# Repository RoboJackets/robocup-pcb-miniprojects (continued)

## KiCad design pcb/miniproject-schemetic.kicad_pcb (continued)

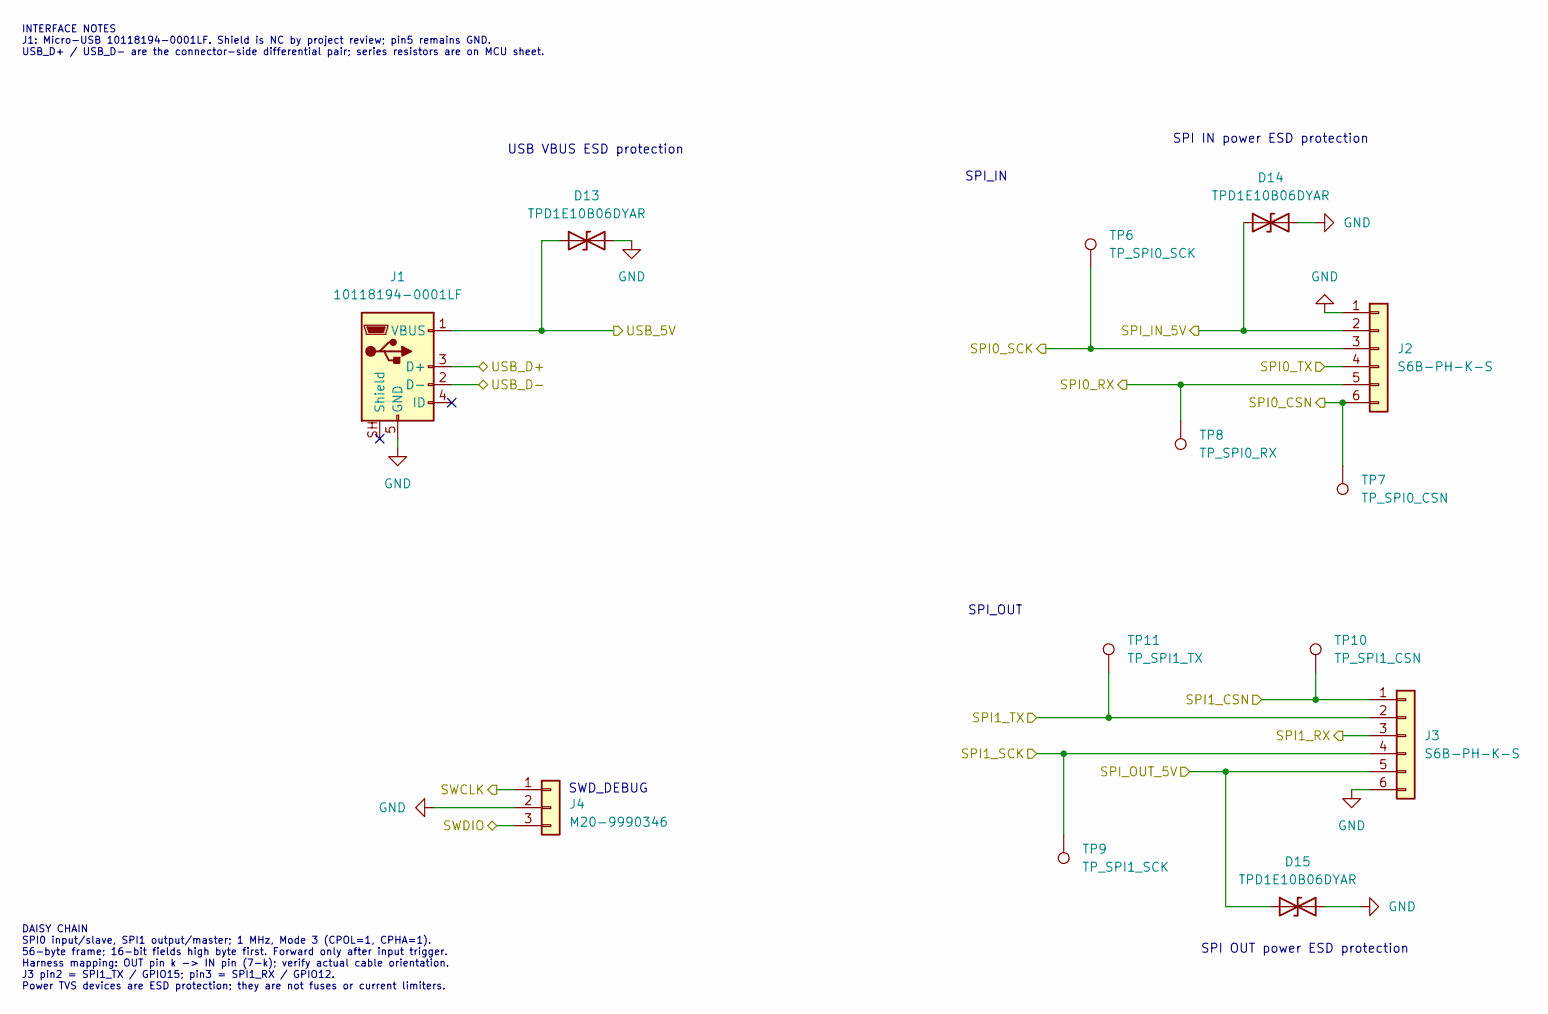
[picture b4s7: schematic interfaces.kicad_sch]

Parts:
D13, D14, D15: TPD1E10B06DYAR; D_SOD-523
J1: 10118194-0001LF; USB_Micro-B_Amphenol_10118194-0001LF_Horizontal
J2, J3: S6B-PH-K-S; JST_PH_S6B-PH-K_1x06_P2.00mm_Horizontal
J4: M20-9990346; PinHeader_1x03_P2.54mm_Vertical
TP6: TP_SPI0_SCK; TestPoint_Pad_D1.0mm
TP7: TP_SPI0_CSN; TestPoint_Pad_D1.0mm
TP8: TP_SPI0_RX; TestPoint_Pad_D1.0mm
TP9: TP_SPI1_SCK; TestPoint_Pad_D1.0mm
TP10: TP_SPI1_CSN; TestPoint_Pad_D1.0mm
TP11: TP_SPI1_TX; TestPoint_Pad_D1.0mm

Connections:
+5V: D15.1 (A1), J3.5; also elsewhere on the board
/Interfaces/USB_D+: J1.3 (D+); also elsewhere on the board
/Interfaces/USB_D-: J1.2 (D-); also elsewhere on the board
/SPI0_CSN: J2.6, TP7.1 (1_1); also elsewhere on the board
/SPI0_RX: J2.5, TP8.1 (1_1); also elsewhere on the board
/SPI0_SCK: J2.3, TP6.1 (1_1); also elsewhere on the board
/SPI0_TX: J2.4; also elsewhere on the board
/SPI1_CSN: J3.1, TP10.1 (1_1); also elsewhere on the board
/SPI1_RX: J3.3; also elsewhere on the board
/SPI1_SCK: J3.4, TP9.1 (1_1); also elsewhere on the board
/SPI1_TX: J3.2, TP11.1 (1_1); also elsewhere on the board
/SPI_IN_5V: D14.1 (A1), J2.2; also elsewhere on the board
/SWCLK: J4.1; also elsewhere on the board
/SWDIO: J4.3; also elsewhere on the board
/USB_5V: D13.1 (A1), J1.1 (VBUS); also elsewhere on the board
GND: D13.2 (A2), D14.2 (A2), D15.2 (A2), J1.5 (GND), J2.1, J3.6, J4.2; also elsewhere on the board

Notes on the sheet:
USB VBUS ESD protection
SPI_IN
SPI OUT power ESD protection
SPI IN power ESD protection
SPI_OUT
SWD_DEBUG
INTERFACE NOTES J1: Micro-USB 10118194-0001LF. Shield is NC by project review; pin5 remains GND. USB_D+ / USB_D- are the connector-side differential pair; series resistors are on MCU sheet.
DAISY CHAIN SPI0 input/slave, SPI1 output/master; 1 MHz, Mode 3 (CPOL=1, CPHA=1). 56-byte frame; 16-bit fields high byte first. Forward only after input trigger. Harness mapping: OUT pin k -> IN pin (7-k); verify actual cable orientation. J3 pin2 = SPI1_TX / GPIO15; pin3 = SPI1_RX / GPIO12. Power T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

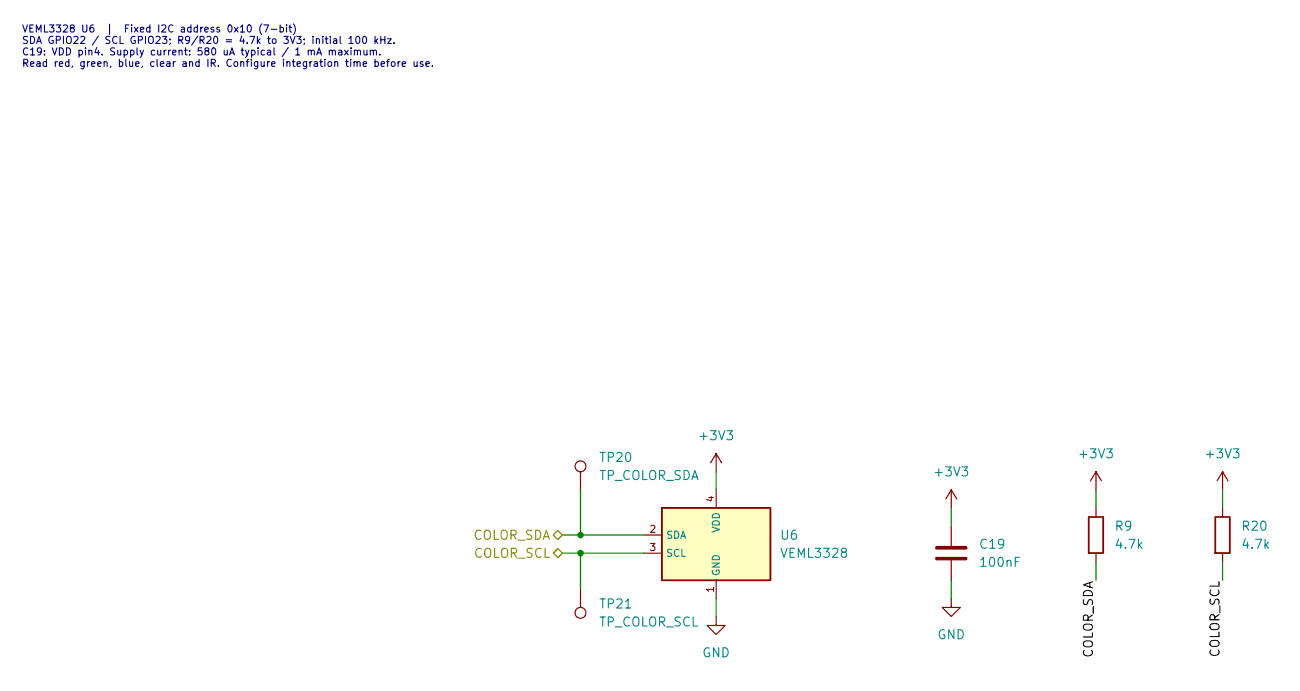
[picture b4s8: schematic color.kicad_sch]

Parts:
C19: 100nF; C_0603_1608Metric; Tolerance 10%; Voltage 6.3V minimum
R9, R20: 4.7k; R_0603_1608Metric; Tolerance 1%
TP20: TP_COLOR_SDA; TestPoint_Pad_D1.0mm
TP21: TP_COLOR_SCL; TestPoint_Pad_D1.0mm
U6: VEML3328; Vishay_VEML3328_2x1.25mm

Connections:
+3V3: C19.1, R9.1, R20.1, U6.4 (VDD); also elsewhere on the board
/COLOR_SCL: R20.2, TP21.1 (1_1), U6.3 (SCL); also elsewhere on the board
/COLOR_SDA: R9.2, TP20.1 (1_1), U6.2 (SDA); also elsewhere on the board
GND: C19.2, U6.1 (GND); also elsewhere on the board

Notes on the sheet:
VEML3328 U6 | Fixed I2C address 0x10 (7-bit) SDA GPIO22 / SCL GPIO23; R9/R20 = 4.7k to 3V3; initial 100 kHz. C19: VDD pin4. Supply current: 580 uA typical / 1 mA maximum. Read red, green, blue, clear and IR. Configure integration time before use.

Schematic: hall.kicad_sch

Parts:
C17: 100nF; C_0603_1608Metric; Tolerance 10%; Voltage 6.3V minimum
R15, R16, R17: 4.7k; R_0603_1608Metric; Tolerance 1%
TP18: TP_HALL_SCL; TestPoint_Pad_D1.0mm
TP19: TP_HALL_SDA; TestPoint_Pad_D1.0mm
U4: TMAG5273A2QDBVR; SOT-23-6

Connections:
+3V3: C17.1, R15.2, R16.1, R17.1, U4.4 (VCC); also elsewhere on the board
/HALL_SCL: R15.1, TP18.1 (1_1), U4.1 (SCL); also elsewhere on the board
/HALL_SDA: R16.2, TP19.1 (1_1), U4.6 (SDA); also elsewhere on the board
GND: C17.2, U4.2 (GND), U4.3 (TEST); also elsewhere on the board
unnamed: R17.2, U4.5 (~INT)

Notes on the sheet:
TMAG5273A2 U4 | Factory I2C address 0x35 (7-bit) SDA GPIO20 / SCL GPIO21; R15/R16 = 4.7k to 3V3; initial 100 kHz. A2 range option: +/-133 mT or +/-266 mT. Active current: 2.3 mA typical. C17: VCC pin4; TEST pin3 is GND. INT pin5 has R17 pullup only, no MCU IRQ. Firmware: INT_MODE = 0; use I2C trigg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

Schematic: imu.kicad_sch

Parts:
C20: 10nF; C_0603_1608Metric; Tolerance 10%; Voltage 6.3V minimum
C21: 100nF; C_0603_1608Metric; Tolerance 10%; Voltage 6.3V minimum
C22: 2.2µF; C_0603_1608Metric; Tolerance 10%; Voltage 6.3V minimum
R21, R22: 4.7k; R_0603_1608Metric; Tolerance 1%
TP14: TP_IMU_SDA; TestPoint_Pad_D1.0mm
TP15: TP_IMU_SCL; TestPoint_Pad_D1.0mm
U7: ICM-42605; LGA-14_3x2.5mm_P0.5mm_LayoutBorder3x4y

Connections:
+3V3: C20.1, C21.1, C22.1, R21.1, R22.1, U7.5 (VDDIO), U7.8 (VDD), U7.12 (~AP_CS); also elsewhere on the board
/IMU_SCL: R22.2, TP15.1 (1_1), U7.13 (AP_SCL); also elsewhere on the board
/IMU_SDA: R21.2, TP14.1 (1_1), U7.14 (AP_SDA); also elsewhere on the board
GND: C20.2, C21.2, C22.2, U7.1 (AP_AD0/SDO), U7.6 (GND), U7.7 (RESV), U7.9 (INT2/FSYNC); also elsewhere on the board

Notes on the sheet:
VDDIO, pin5
VDD, pin8
ICM-42605 U7 | I2C address 0x68 (7-bit), AP_AD0 pin1 = GND AP_CS pin12 = 3V3 for I2C. SDA GPIO16 / SCL GPIO17; R21/R22 = 4.7k. Initial bus speed 100 kHz. AP_AD0 is an input in this configuration. INT1 pin4 is NC. Pin9 is unused FSYNC: GND per TDK pin-function table. Firmware must keep pin9 as an in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

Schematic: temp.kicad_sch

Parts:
C18: 100nF; C_0603_1608Metric; Tolerance 10%; Voltage 6.3V minimum
R18, R19: 4.7k; R_0603_1608Metric; Tolerance 1%
TP16: TP_TEMP_SDA; TestPoint_Pad_D1.0mm
TP17: TP_TEMP_SCL; TestPoint_Pad_D1.0mm
U5: LM75ADP; TSSOP-8_3x3mm_P0.65mm

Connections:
+3V3: C18.1, R18.1, R19.1, U5.8 (VCC); also elsewhere on the board
/TEMP_SCL: R19.2, TP17.1 (1_1), U5.2 (SCL); also elsewhere on the board
/TEMP_SDA: R18.2, TP16.1 (1_1), U5.1 (SDA); also elsewhere on the board
GND: C18.2, U5.4 (GND), U5.5 (A2), U5.6 (A1), U5.7 (A0); also elsewhere on the board

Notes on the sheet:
LM75ADP U5 | I2C address 0x48 (7-bit), A2:A0 = 000 SDA GPIO18 / SCL GPIO19; R18/R19 = 4.7k to 3V3; initial 100 kHz. C18: VCC pin8. OS pin3 is NC; poll temperature over I2C. Supply current: 100 uA typical with inactive bus; 1 mA maximum with active bus. NXP LM75A register format: signed temperature;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

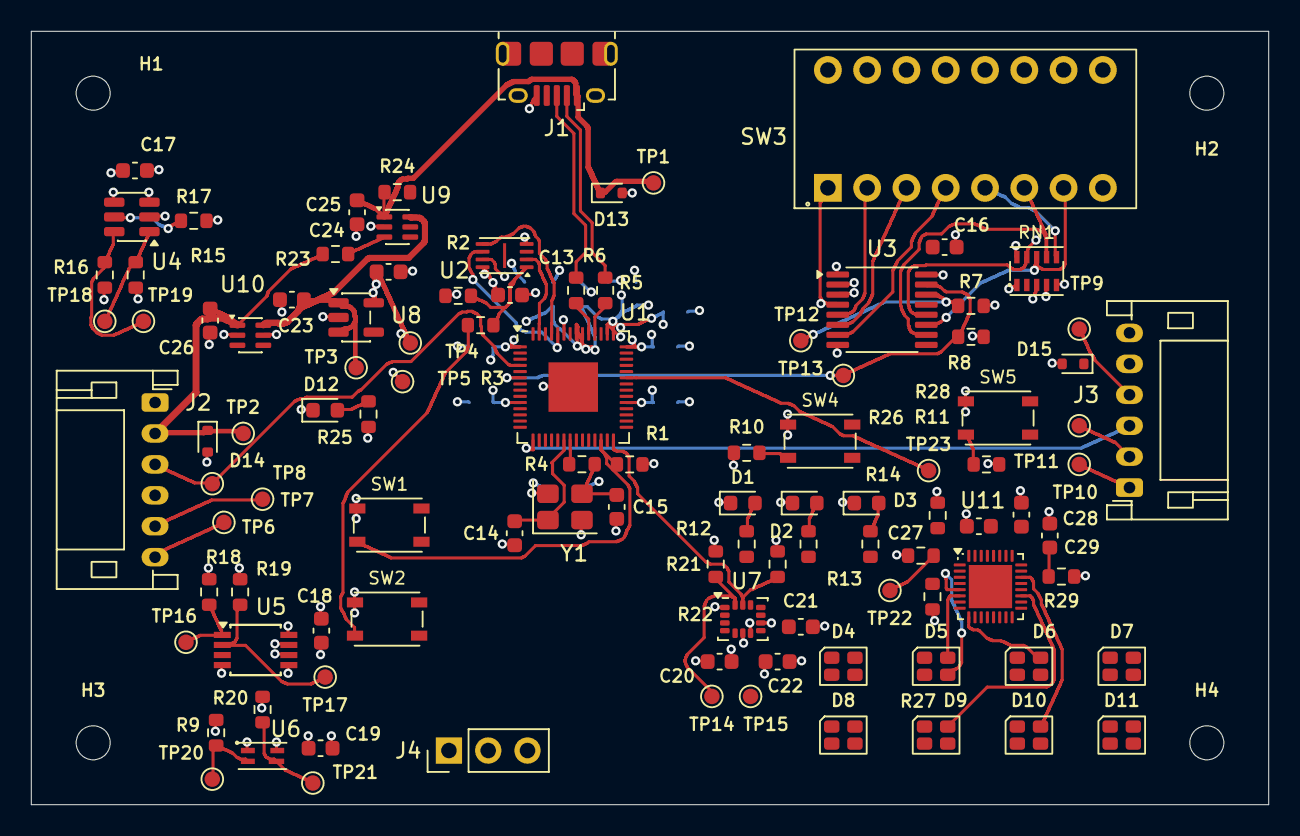
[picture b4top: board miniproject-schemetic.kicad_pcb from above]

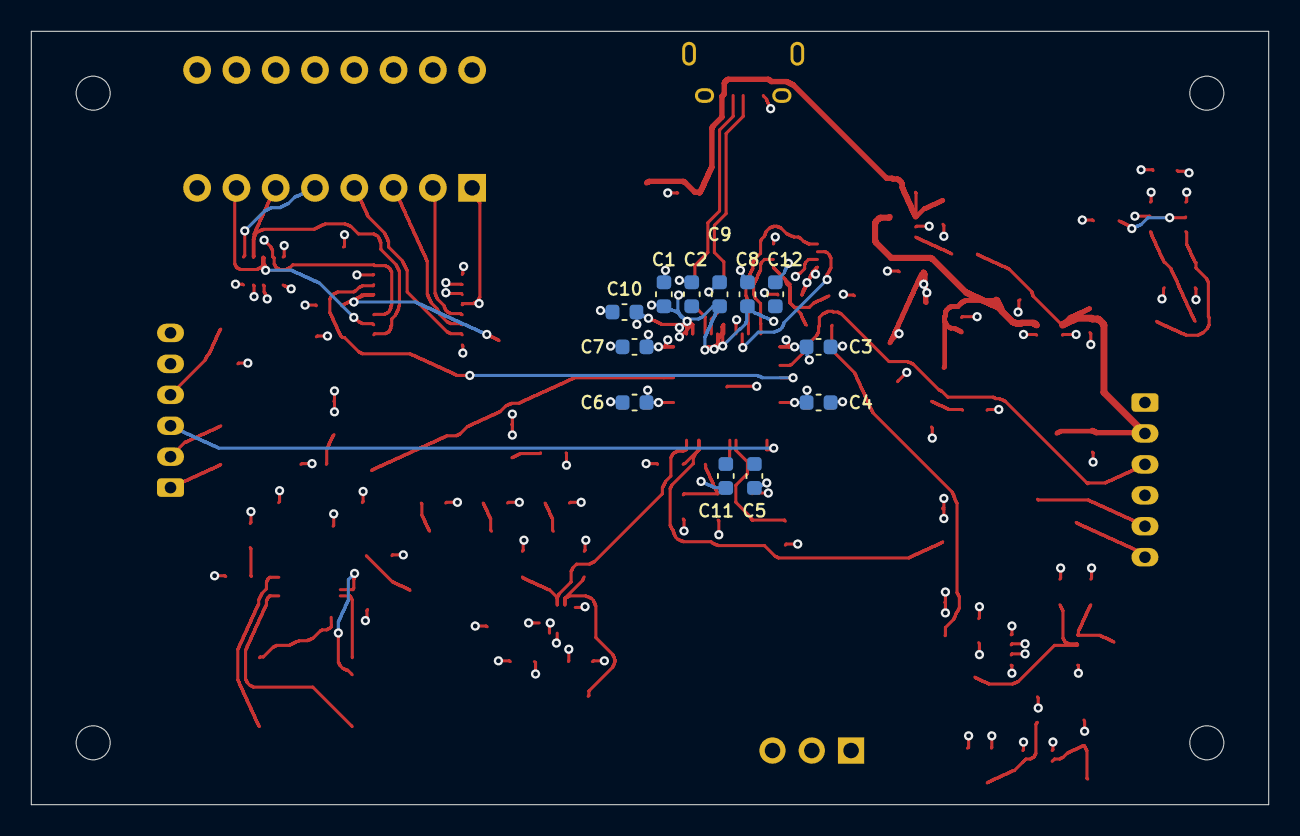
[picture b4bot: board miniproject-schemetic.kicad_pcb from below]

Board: 4 copper layers, 80.0 x 50.0 mm, 122 parts (12 on the bottom side), 89 nets.

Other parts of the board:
H1, H2, H3, H4: MountingHole_2.2mm_M2

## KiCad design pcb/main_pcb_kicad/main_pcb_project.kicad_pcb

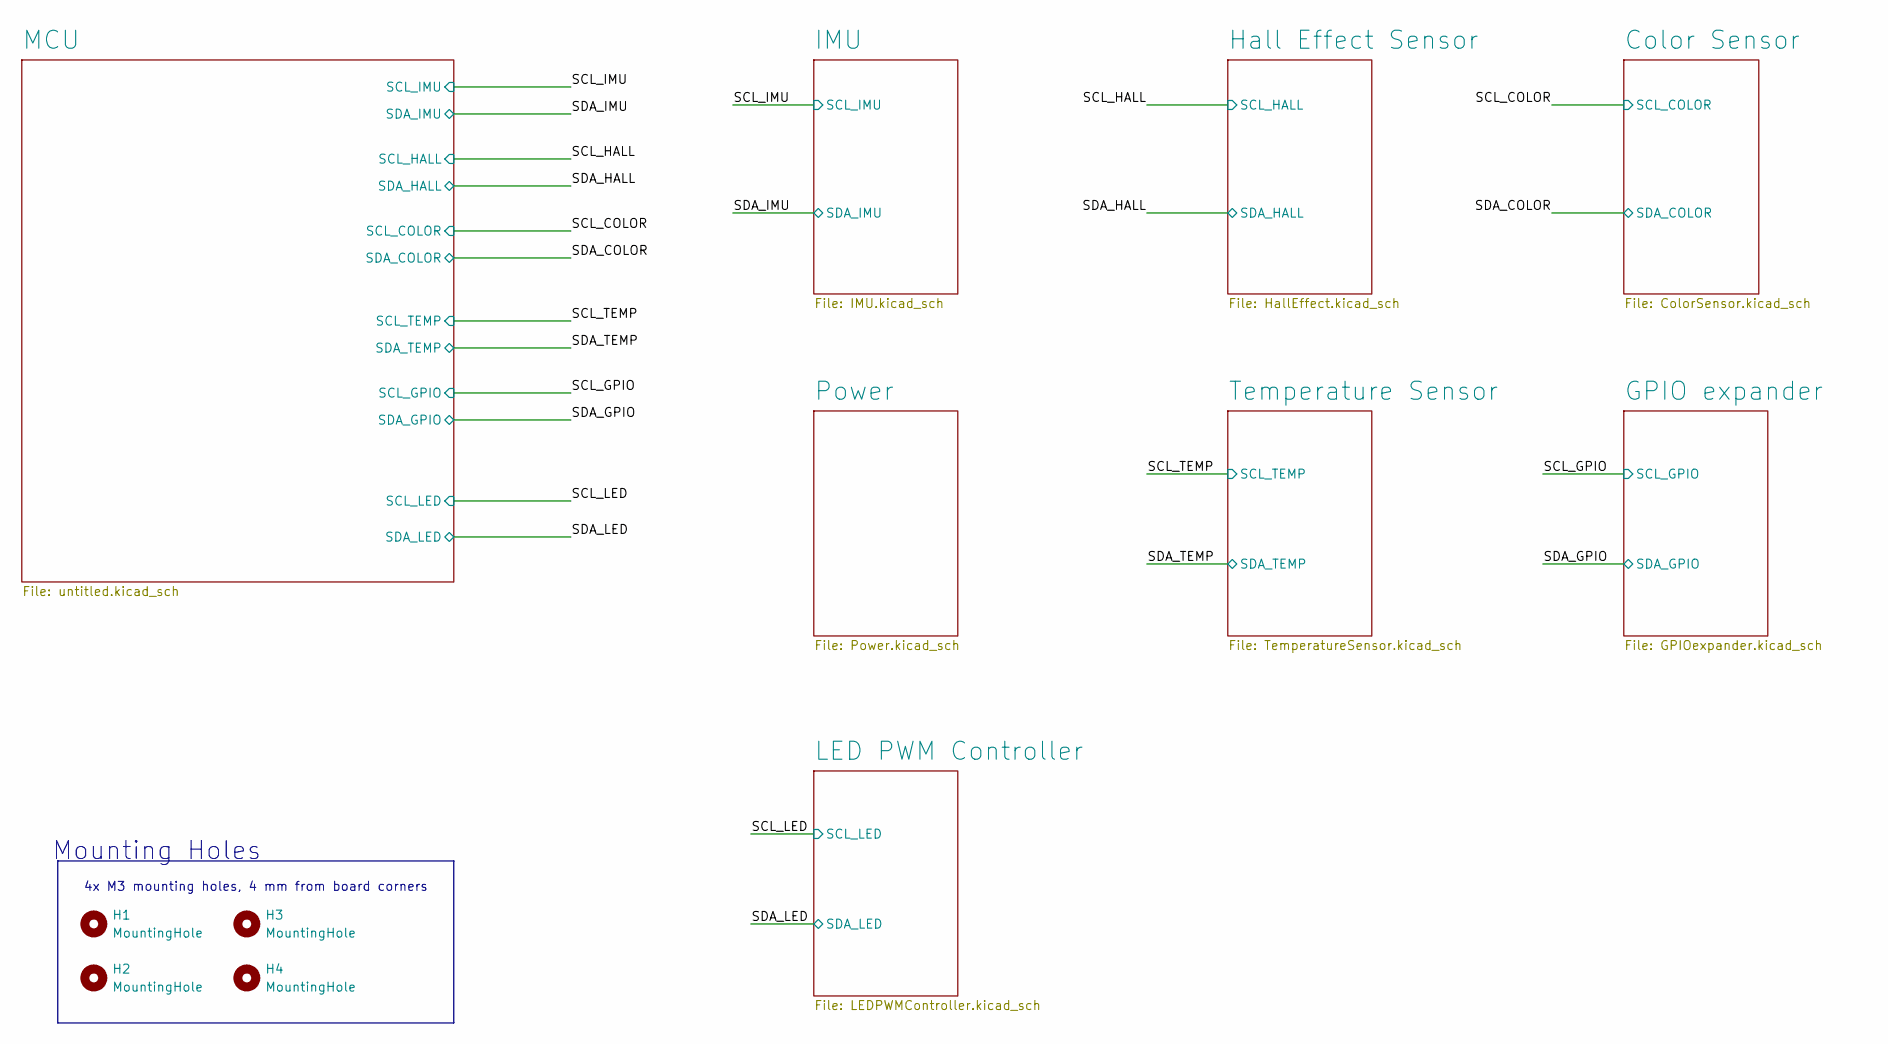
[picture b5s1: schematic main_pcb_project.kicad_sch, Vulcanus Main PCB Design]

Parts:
H1, H2, H3, H4: MountingHole; MountingHole_3.2mm_M3

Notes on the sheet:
Mounting Holes
4x M3 mounting holes, 4 mm from board corners

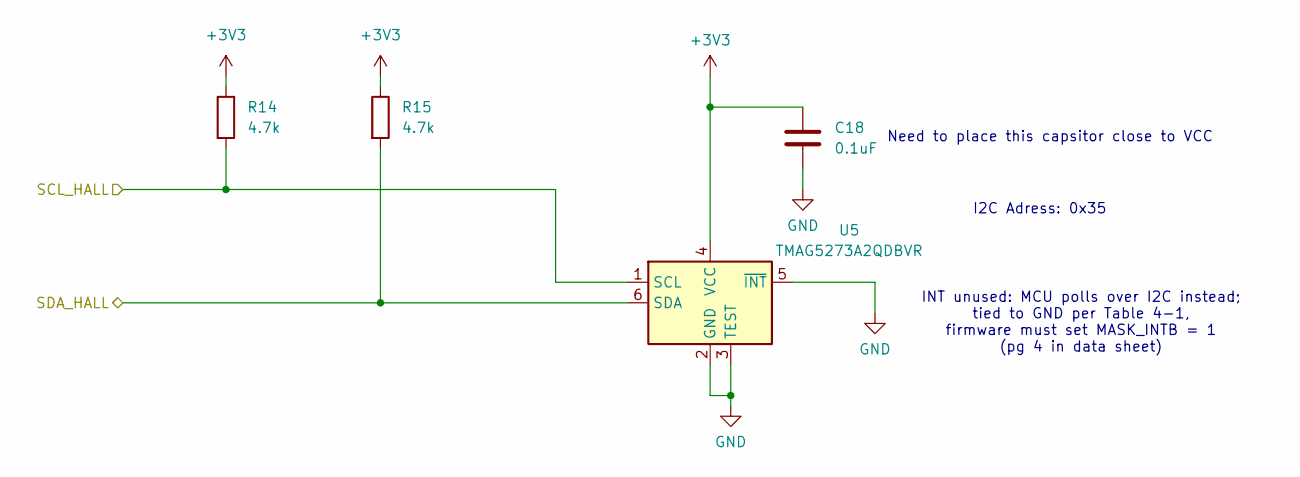
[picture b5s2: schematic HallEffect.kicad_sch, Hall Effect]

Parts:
C18: 0.1uF; C_0603_1608Metric; Manufacturer P/N CL10B104KB8NNNC
R14, R15: 4.7k; R_0402_1005Metric; Manufacturer P/N RC0402FR-074K7L
U5: TMAG5273A2QDBVR; SOT-23-6; Manufacturer P/N TMAG5273A2QDBVR

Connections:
+3V3: C18.1, R14.1, R15.1, U5.4 (VCC); also elsewhere on the board
/SCL_HALL: R14.2, U5.1 (SCL); also elsewhere on the board
/SDA_HALL: R15.2, U5.6 (SDA); also elsewhere on the board
GND: C18.2, U5.2 (GND), U5.3 (TEST), U5.5 (~INT); also elsewhere on the board

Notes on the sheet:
INT unused: MCU polls over I2C instead; tied to GND per Table 4-1, firmware must set MASK_INTB = 1 (pg 4 in data sheet)
Need to place this capsitor close to VCC
I2C Adress: 0x35

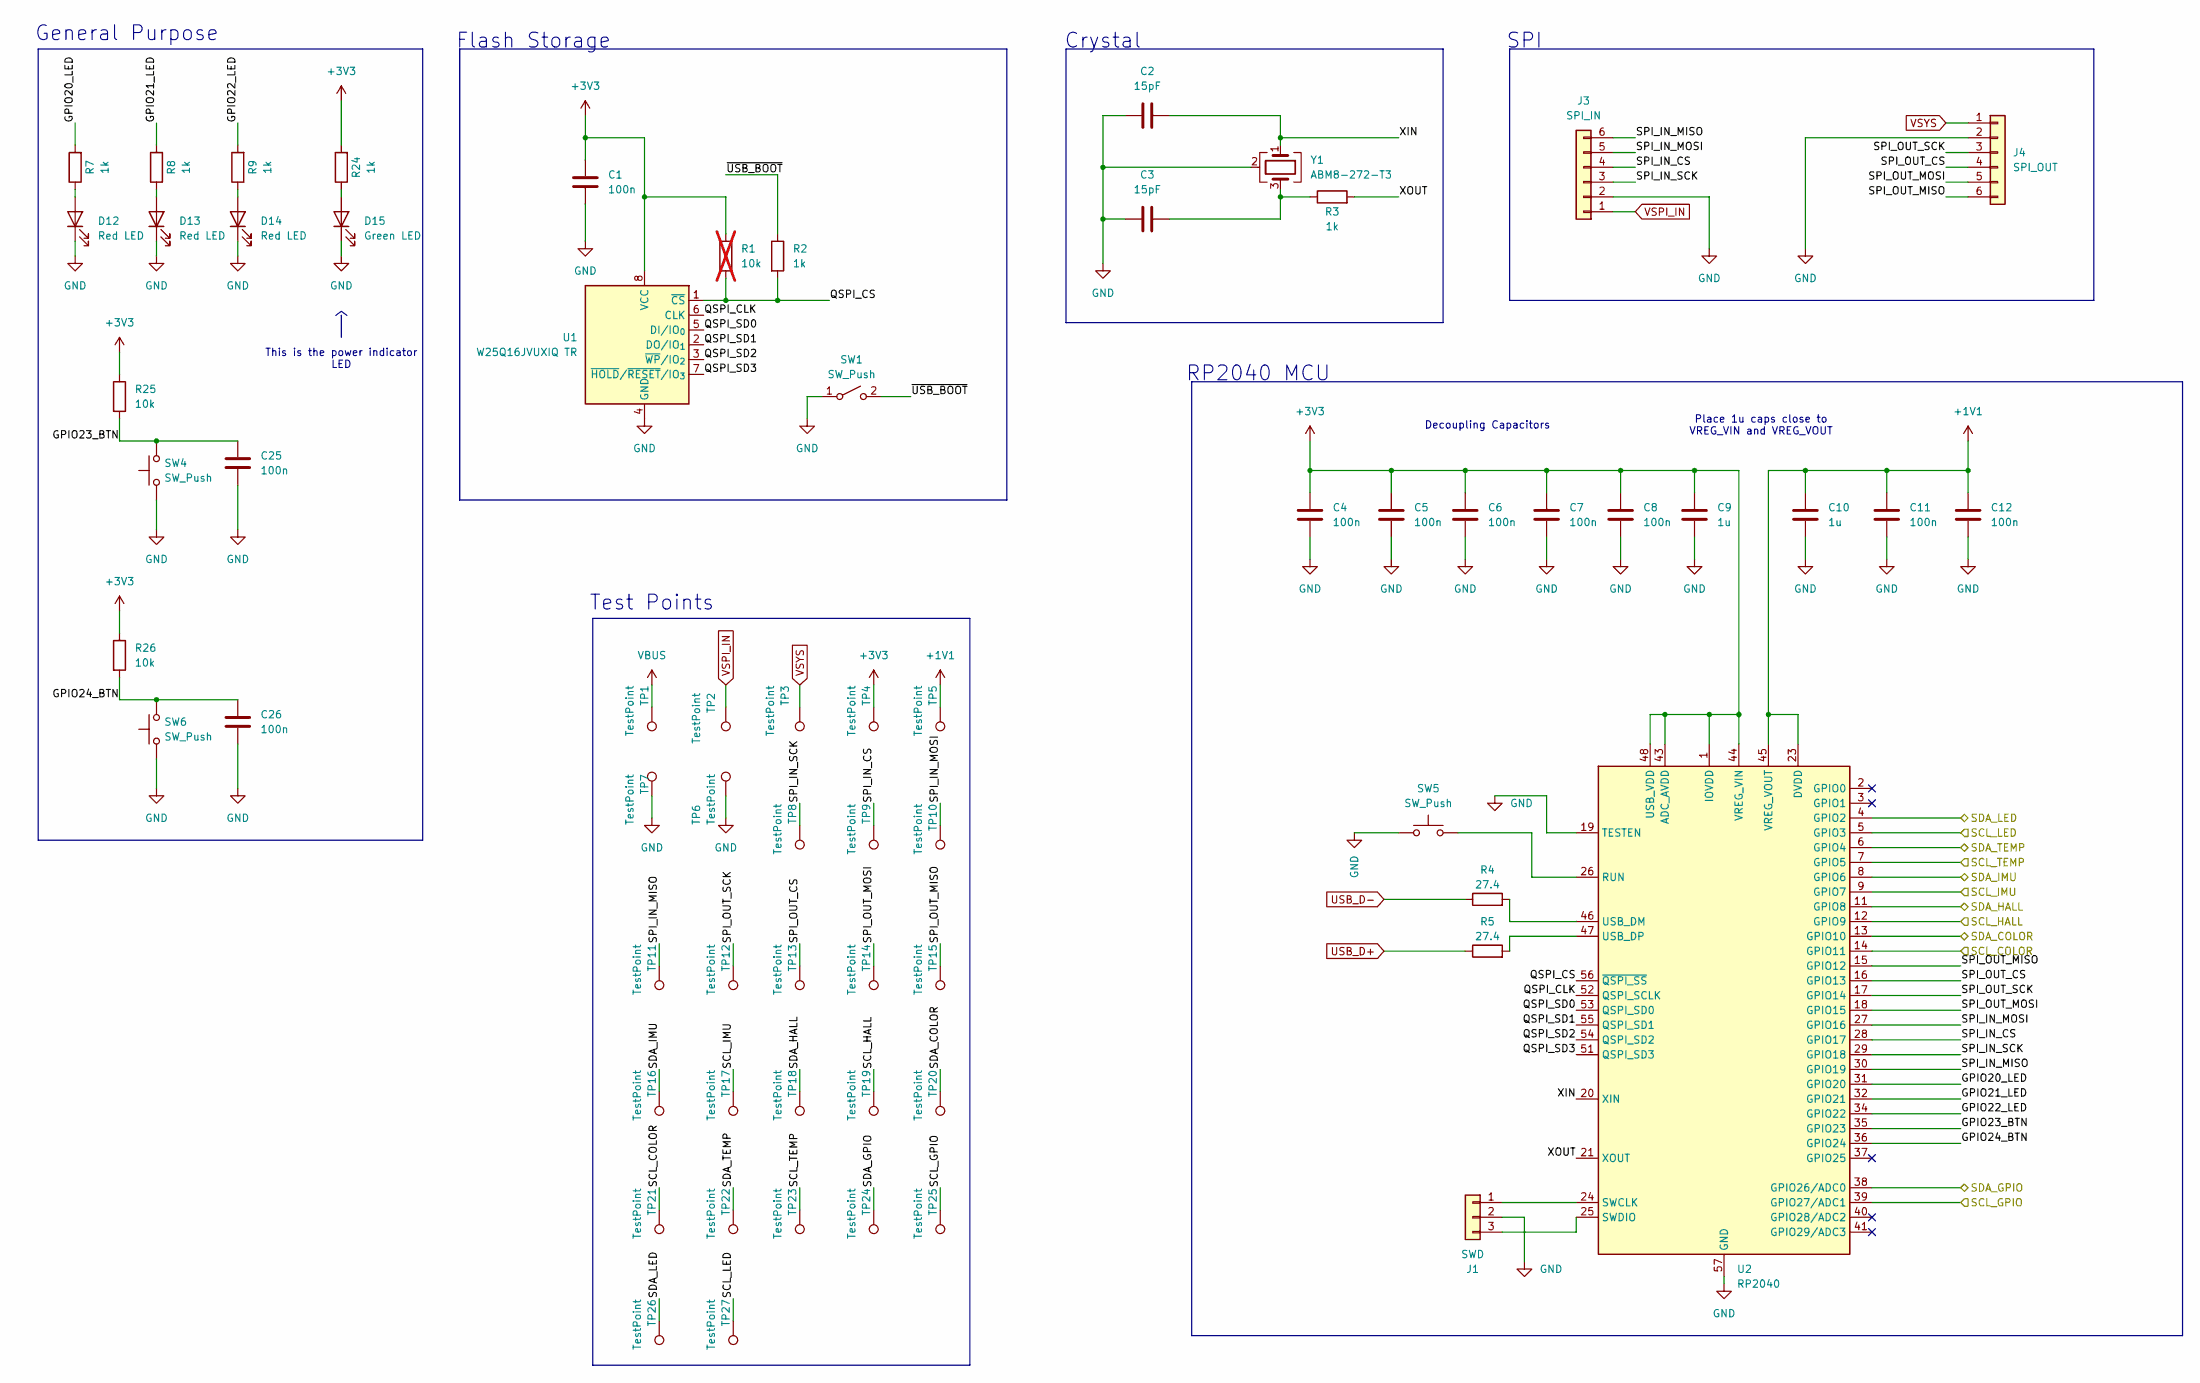
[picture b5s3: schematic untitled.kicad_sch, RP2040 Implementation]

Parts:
C1: 100n; C_0402_1005Metric
C2, C3: 15pF; C_0603_1608Metric; Manufacturer P/N C0603C150F5GACTU
C4, C5, C6, C7, C8, C11, C12: 100n; C_0402_1005Metric; Manufacturer P/N CC0603KRX7R9BB104
C9, C10: 1u; C_0402_1005Metric; Manufacturer P/N CL10A105KO8NNNC
C25, C26: 100n; C_0603_1608Metric; Manufacturer P/N CC0603KRX7R9BB104
D12, D13, D14: Red LED; LED_0603_1608Metric; Manufacturer P/N LTST-C191KRKT
D15: Green LED; LED_0603_1608Metric; Manufacturer P/N LTST-C191KGKT
J1: SWD; PinHeader_1x03_P2.54mm_Vertical; Manufacturer P/N PRPC003SAAN-RC
J3: SPI_IN; JST_PH_S6B-PH-K_1x06_P2.00mm_Horizontal; Manufacturer P/N S6B-PH-K-S
J4: SPI_OUT; JST_PH_S6B-PH-K_1x06_P2.00mm_Horizontal; Manufacturer P/N S6B-PH-K-S
R1: 10k; R_0402_1005Metric; Manufacturer P/N RC0402FR-0710KL; not fitted
R2, R3, R7, R8, R9, R24: 1k; R_0402_1005Metric; Manufacturer P/N RC0402FR-071KL
R4, R5: 27.4; R_0402_1005Metric; Manufacturer P/N RC0402FR-0727R4L
R25, R26: 10k; R_0402_1005Metric; Manufacturer P/N RC0402FR-0710KL
SW1: SW_Push; SW_SKRPACE010_AAL; Manufacturer P/N SKRPACE010
SW4, SW5, SW6: SW_Push; SW_SKRPACE010_AAL; Manufacturer P/N SKRPABE010
TP1, TP2, TP3, TP4, TP5, TP6, TP7, TP8, TP9, TP10, TP11, TP12, TP13, TP14, TP15, TP16, TP17, TP18, TP19, TP20, TP21, TP22, TP23, TP24, TP25, TP26, TP27: TestPoint; TestPoint_Pad_D1.0mm
U1: W25Q16JVUXIQ TR; Winbond_USON-8-1EP_3x2mm_P0.5mm_EP0.2x1.6mm; Manufacturer P/N W25Q16JVUXIQ TR
U2: RP2040; QFN-56-1EP_7x7mm_P0.4mm_EP3.2x3.2mm; Manufacturer P/N SC0914(13)
Y1: ABM8-272-T3; Crystal_SMD_3225-4Pin_3.2x2.5mm; Manufacturer P/N ABM8-272-T3

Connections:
+1V1: C10.1, C11.1, C12.1, TP5.1 (1_1), U2.23 (DVDD), U2.45 (VREG_VOUT), U2.50 (DVDD)
+3V3: C1.1, C4.1, C5.1, C6.1, C7.1, C8.1, C9.1, R1.1, R24.2, R25.1, R26.1, TP4.1 (1_1), U1.8 (VCC), U2.1 (IOVDD), U2.10 (IOVDD), U2.22 (IOVDD), U2.33 (IOVDD), U2.42 (IOVDD), U2.43 (ADC_AVDD), U2.44 (VREG_VIN), U2.48 (USB_VDD), U2.49 (IOVDD); also elsewhere on the board
/MCU/GPIO20_LED: R7.2, U2.31 (GPIO20)
/MCU/GPIO21_LED: R8.2, U2.32 (GPIO21)
/MCU/GPIO22_LED: R9.2, U2.34 (GPIO22)
/MCU/GPIO23_BTN: C25.1, R25.2, SW4.2, U2.35 (GPIO23)
/MCU/GPIO24_BTN: C26.1, R26.2, SW6.2, U2.36 (GPIO24)
/MCU/QSPI_CLK: U1.6 (CLK), U2.52 (QSPI_SCLK)
/MCU/QSPI_CS: R1.2, R2.2, U1.1 (~CS), U2.56 (~QSPI_SS)
/MCU/QSPI_SD0: U1.5 (DI/IO_{0}), U2.53 (QSPI_SD0)
/MCU/QSPI_SD1: U1.2 (DO/IO_{1}), U2.55 (QSPI_SD1)
/MCU/QSPI_SD2: U1.3 (~WP/IO_{2}), U2.54 (QSPI_SD2)
/MCU/QSPI_SD3: U1.7 (~HOLD/~RESET/IO_{3}), U2.51 (QSPI_SD3)
/MCU/SPI_IN_CS: J3.4, TP9.1 (1_1), U2.28 (GPIO17)
/MCU/SPI_IN_MISO: J3.6, TP11.1 (1_1), U2.30 (GPIO19)
/MCU/SPI_IN_MOSI: J3.5, TP10.1 (1_1), U2.27 (GPIO16)
/MCU/SPI_IN_SCK: J3.3, TP8.1 (1_1), U2.29 (GPIO18)
/MCU/SPI_OUT_CS: J4.4, TP13.1 (1_1), U2.16 (GPIO13)
/MCU/SPI_OUT_MISO: J4.6, TP15.1 (1_1), U2.15 (GPIO12)
/MCU/SPI_OUT_MOSI: J4.5, TP14.1 (1_1), U2.18 (GPIO15)
/MCU/SPI_OUT_SCK: J4.3, TP12.1 (1_1), U2.17 (GPIO14)
/MCU/XIN: C2.2, U2.20 (XIN), Y1.1
/MCU/XOUT: R3.2, U2.21 (XOUT)
/MCU/~USB_BOOT: R2.1, SW1.2 (B)
/SCL_COLOR: TP21.1 (1_1), U2.14 (GPIO11); also elsewhere on the board
/SCL_GPIO: TP25.1 (1_1), U2.39 (GPIO27/ADC1); also elsewhere on the board
/SCL_HALL: TP19.1 (1_1), U2.12 (GPIO9); also elsewhere on the board
/SCL_IMU: TP17.1 (1_1), U2.9 (GPIO7); also elsewhere on the board
/SCL_LED: TP27.1 (1_1), U2.5 (GPIO3); also elsewhere on the board
/SCL_TEMP: TP23.1 (1_1), U2.7 (GPIO5); also elsewhere on the board
/SDA_COLOR: TP20.1 (1_1), U2.13 (GPIO10); also elsewhere on the board
/SDA_GPIO: TP24.1 (1_1), U2.38 (GPIO26/ADC0); also elsewhere on the board
/SDA_HALL: TP18.1 (1_1), U2.11 (GPIO8); also elsewhere on the board
/SDA_IMU: TP16.1 (1_1), U2.8 (GPIO6); also elsewhere on the board
/SDA_LED: TP26.1 (1_1), U2.4 (GPIO2); also elsewhere on the board
/SDA_TEMP: TP22.1 (1_1), U2.6 (GPIO4); also elsewhere on the board
GND: C1.2, C2.1, C3.1, C4.2, C5.2, C6.2, C7.2, C8.2, C9.2, C10.2, C11.2, C12.2, C25.2, C26.2, D12.1 (K), D13.1 (K), D14.1 (K), D15.1 (K), J1.2, J3.2, J4.2, SW1.1 (A), SW4.1, SW5.1, SW6.1, TP6.1 (1_1), TP7.1 (1_1), U1.4 (GND), U2.19 (TESTEN), U2.57 (GND), Y1.2 (G), Y1.4 (G); also elsewhere on the board
unnamed: C3.2, R3.1, Y1.3
unnamed: D12.2 (A), R7.1
unnamed: D13.2 (A), R8.1
unnamed: D14.2 (A), R9.1
unnamed: D15.2 (A), R24.1
unnamed: J1.1, U2.24 (SWCLK)
unnamed: J1.3, U2.25 (SWDIO)
unnamed: SW5.2, U2.26 (RUN)
unnamed: R4.2, U2.46 (USB_DM)
unnamed: R5.2, U2.47 (USB_DP)
USB_D+: R5.1; also elsewhere on the board
USB_D-: R4.1; also elsewhere on the board
VBUS: TP1.1 (1_1); also elsewhere on the board
VSPI_IN: J3.1, TP2.1 (1_1); also elsewhere on the board
VSYS: J4.1, TP3.1 (1_1); also elsewhere on the board

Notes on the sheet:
General Purpose
Crystal
SPI
RP2040 MCU
Test Points
Place 1u caps close to VREG_VIN and VREG_VOUT
Decoupling Capacitors
This is the power indicator LED
Flash Storage

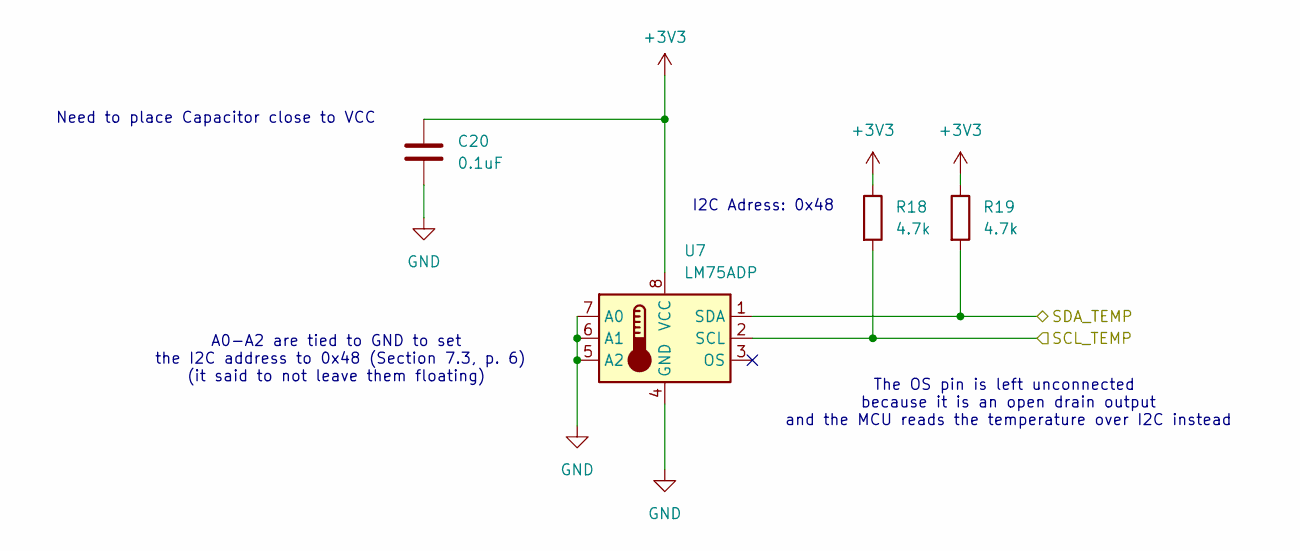
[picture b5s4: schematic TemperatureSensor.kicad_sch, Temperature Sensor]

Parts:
C20: 0.1uF; C_0603_1608Metric; Manufacturer P/N CL10B104KB8NNNC
R18, R19: 4.7k; R_0402_1005Metric; Manufacturer P/N RC0402FR-074K7L
U7: LM75ADP; TSSOP-8_3x3mm_P0.65mm; Manufacturer P/N LM75ADP,118

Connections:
+3V3: C20.1, R18.1, R19.1, U7.8 (VCC); also elsewhere on the board
/SCL_TEMP: R18.2, U7.2 (SCL); also elsewhere on the board
/SDA_TEMP: R19.2, U7.1 (SDA); also elsewhere on the board
GND: C20.2, U7.4 (GND), U7.5 (A2), U7.6 (A1), U7.7 (A0); also elsewhere on the board

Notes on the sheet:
I2C Adress: 0x48
The OS pin is left unconnected because it is an open drain output and the MCU reads the temperature over I2C instead
A0-A2 are tied to GND to set the I2C address to 0x48 (Section 7.3, p. 6) (it said to not leave them floating)
Need to place Capacitor close to VCC

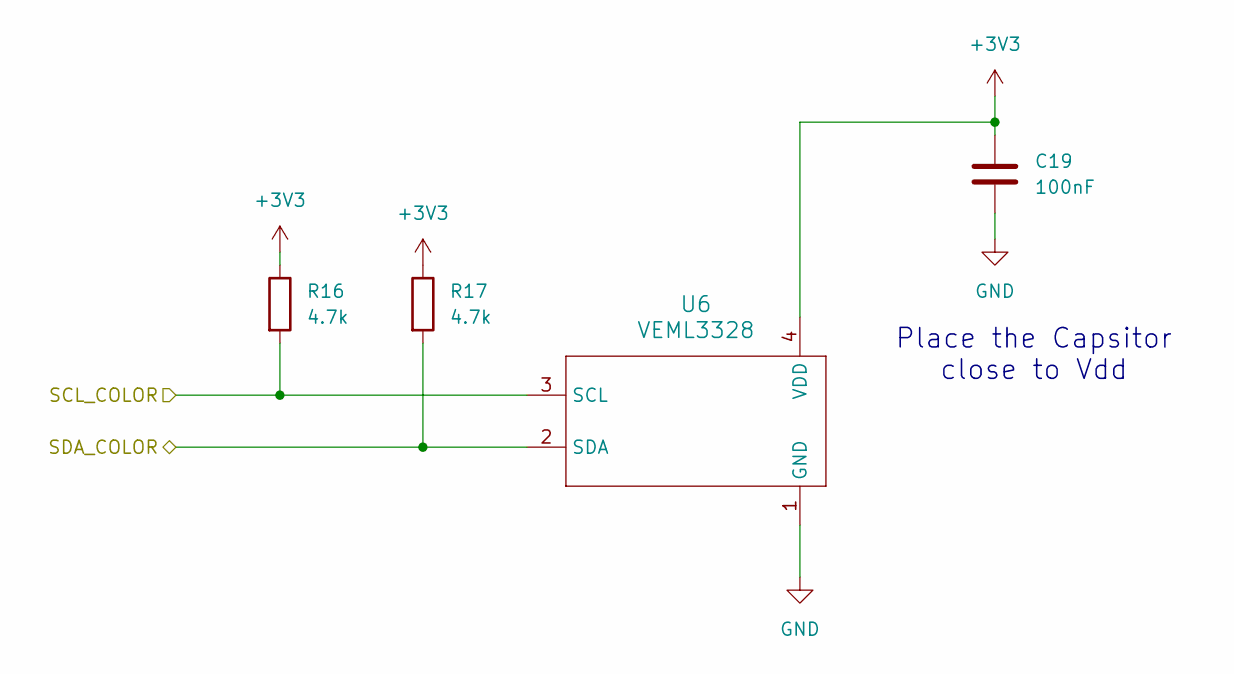
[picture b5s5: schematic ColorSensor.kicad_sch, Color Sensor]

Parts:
C19: 100nF; C_0603_1608Metric; Manufacturer P/N CC0603KRX7R9BB104
R16, R17: 4.7k; R_0402_1005Metric; Manufacturer P/N RC0402FR-074K7L
U6: VEML3328; SMD_L3328_VIS; Manufacturer P/N VEML3328

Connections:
+3V3: C19.1, R16.1, R17.1, U6.4 (VDD); also elsewhere on the board
/SCL_COLOR: R16.2, U6.3 (SCL); also elsewhere on the board
/SDA_COLOR: R17.2, U6.2 (SDA); also elsewhere on the board
GND: C19.2, U6.1 (GND); also elsewhere on the board

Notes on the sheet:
Place the Capsitor close to Vdd

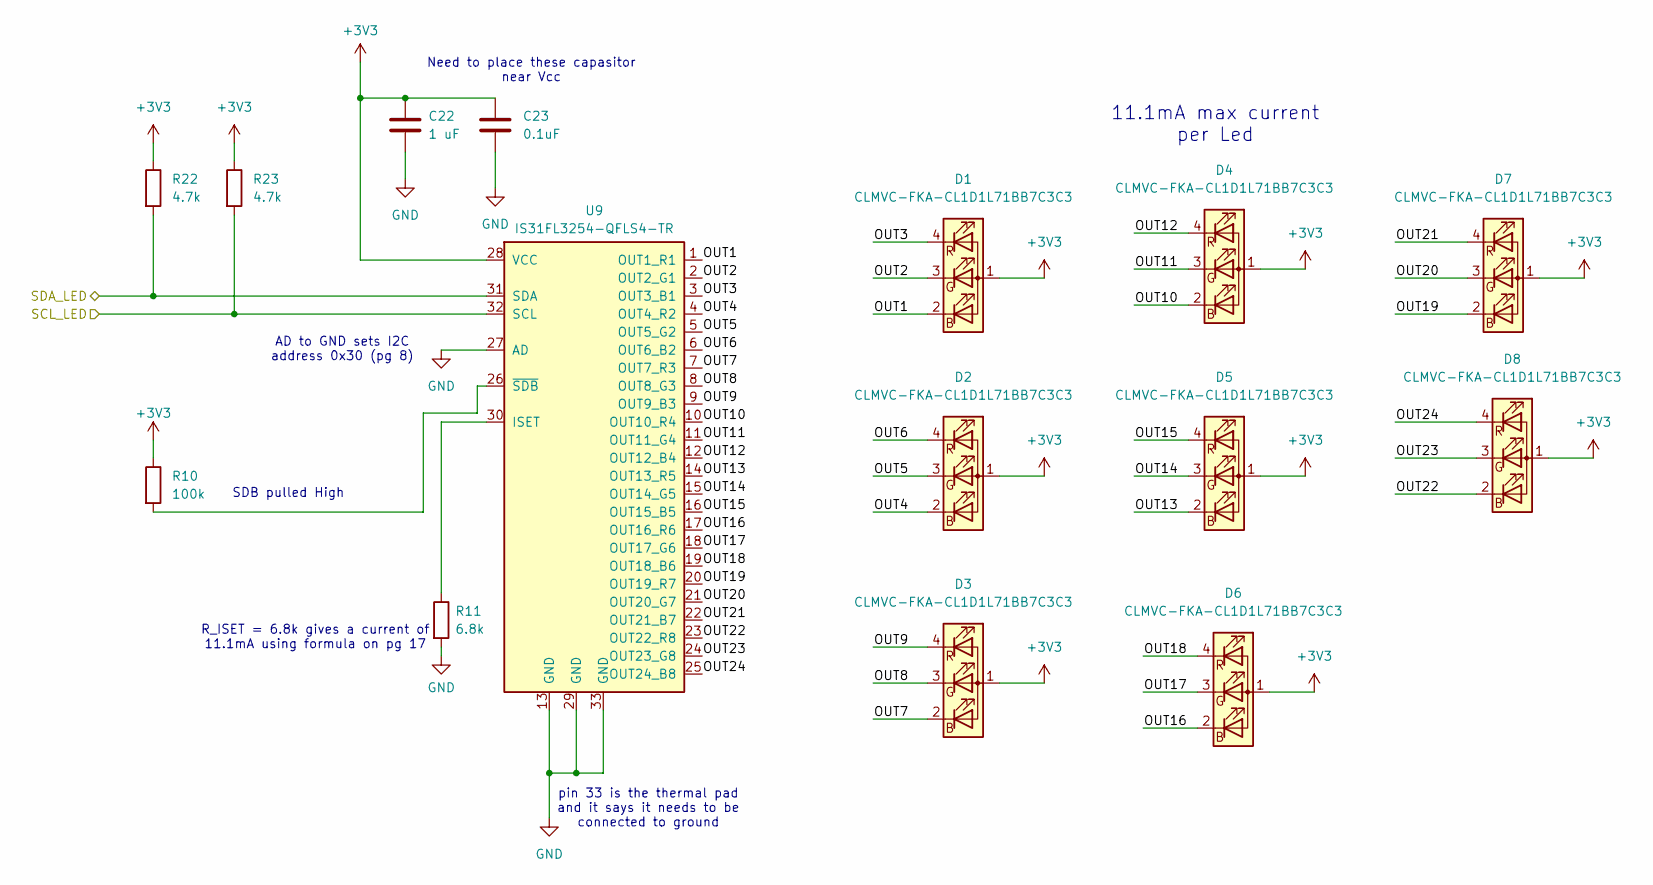
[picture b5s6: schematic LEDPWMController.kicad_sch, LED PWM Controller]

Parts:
C22: 1 uF; C_0603_1608Metric; Manufacturer P/N CC0603KRX7R7BB105
C23: 0.1uF; C_0603_1608Metric; Manufacturer P/N CL10B104KB8NNNC
D1, D2, D3, D4, D5, D6, D7, D8: CLMVC-FKA-CL1D1L71BB7C3C3; LED_Cree-PLCC4_2x2mm_CW; Manufacturer P/N CLMVC-FKA-CL1D1L71BB7C3C3
R10: 100k; R_0402_1005Metric; Manufacturer P/N RC0402FR-07100KL
R11: 6.8k; R_0402_1005Metric; Manufacturer P/N RC0402FR-076K8L
R22, R23: 4.7k; R_0402_1005Metric; Manufacturer P/N RC0402FR-074K7L
U9: IS31FL3254-QFLS4-TR; QFN-32-1EP_4x4mm_P0.4mm_EP2.65x2.65mm; Manufacturer P/N IS31FL3254-QFLS4-TR

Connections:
+3V3: C22.1, C23.1, D1.1 (A), D2.1 (A), D3.1 (A), D4.1 (A), D5.1 (A), D6.1 (A), D7.1 (A), D8.1 (A), R10.1, R22.1, R23.1, U9.28 (VCC); also elsewhere on the board
/LED PWM Controller/OUT1: D1.2 (BK), U9.1 (OUT1_R1)
/LED PWM Controller/OUT2: D1.3 (GK), U9.2 (OUT2_G1)
/LED PWM Controller/OUT3: D1.4 (RK), U9.3 (OUT3_B1)
/LED PWM Controller/OUT4: D2.2 (BK), U9.4 (OUT4_R2)
/LED PWM Controller/OUT5: D2.3 (GK), U9.5 (OUT5_G2)
/LED PWM Controller/OUT6: D2.4 (RK), U9.6 (OUT6_B2)
/LED PWM Controller/OUT7: D3.2 (BK), U9.7 (OUT7_R3)
/LED PWM Controller/OUT8: D3.3 (GK), U9.8 (OUT8_G3)
/LED PWM Controller/OUT9: D3.4 (RK), U9.9 (OUT9_B3)
/LED PWM Controller/OUT10: D4.2 (BK), U9.10 (OUT10_R4)
/LED PWM Controller/OUT11: D4.3 (GK), U9.11 (OUT11_G4)
/LED PWM Controller/OUT12: D4.4 (RK), U9.12 (OUT12_B4)
/LED PWM Controller/OUT13: D5.2 (BK), U9.14 (OUT13_R5)
/LED PWM Controller/OUT14: D5.3 (GK), U9.15 (OUT14_G5)
/LED PWM Controller/OUT15: D5.4 (RK), U9.16 (OUT15_B5)
/LED PWM Controller/OUT16: D6.2 (BK), U9.17 (OUT16_R6)
/LED PWM Controller/OUT17: D6.3 (GK), U9.18 (OUT17_G6)
/LED PWM Controller/OUT18: D6.4 (RK), U9.19 (OUT18_B6)
/LED PWM Controller/OUT19: D7.2 (BK), U9.20 (OUT19_R7)
/LED PWM Controller/OUT20: D7.3 (GK), U9.21 (OUT20_G7)
/LED PWM Controller/OUT21: D7.4 (RK), U9.22 (OUT21_B7)
/LED PWM Controller/OUT22: D8.2 (BK), U9.23 (OUT22_R8)
/LED PWM Controller/OUT23: D8.3 (GK), U9.24 (OUT23_G8)
/LED PWM Controller/OUT24: D8.4 (RK), U9.25 (OUT24_B8)
/SCL_LED: R23.2, U9.32 (SCL); also elsewhere on the board
/SDA_LED: R22.2, U9.31 (SDA); also elsewhere on the board
GND: C22.2, C23.2, R11.2, U9.13 (GND), U9.27 (AD), U9.29 (GND), U9.33 (GND); also elsewhere on the board
unnamed: R11.1, U9.30 (ISET)
unnamed: R10.2, U9.26 (~SDB)

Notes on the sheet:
11.1mA max current per Led
Need to place these capasitor near Vcc
R_ISET = 6.8k gives a current of 11.1mA using formula on pg 17
SDB pulled High
pin 33 is the thermal pad and it says it needs to be connected to ground
AD to GND sets I2C address 0x30 (pg 8)
